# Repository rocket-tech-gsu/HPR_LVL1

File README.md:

# High Powered Rocket Level-1 (HPR Lvl-1):

### Classifying a Rockets according to their total impulse:
- Rockets that goes to moon/mars, or to an earth orbit are called orbital class rockets;
- Those going below 100-250Km are called sounding rockets;
- Below 100Km are called high powered rockets, but they are sub-classified:<br>
  - As per NAR(National Associatoin of Rocketry):

<u>__High Powered Rocketry in the USA:__</u><br>
FAA governs the US air space and have defined some guidelines:<br>
[Amateur Rocketry Guidelines](https://www.faa.gov/air_traffic/publications/atpubs/pham_html/chap31_section_1.html#:~:text=Class%202%20%2D%20a%20high%20power,pound%2Dseconds)

# Software Organization:
__Algorithms:__
- Noise Filtering:
  - Low pass filter
  - Butterworth filter
- Sensor Fusion:
  - State Estimators
  - Kalman filter

to be completed ...

# Design Overview:
to be written ...

# Avionics Overview:
to be written ...

# Future Experimental Functionalities/Payloads(not relevant to the HPR certifications):
- Custom Radio Communication module
- Reaction Wheel for stabilization of the Roll Axis
- Fin Control/Thrust Vector Control

<!-- ## Depricated Gameplan:
Step 1: Shortlist all of the sensors, actuators, microcontrollers, and other hardware components that would be the perfect fit for the given problem statement.<br>
Step 2: Come up with a schematic.<br>
Step 3: Write the program for each individual component.<br>
Step 4: Test all those individual parts of codes with the microcontroller on the breadboard or in the Proteus Software.<br>
Step 5: Integrate all those components together.<br>
Step 6: Perform tests.<br>
Step 7: Design a nice board, and route all the copper traces onto a PCB of the right size and shape.<br>
Step 8: Get the PCB manufactured, or manufacture it yourself.<br>
Step 9: Solder everything together.<br>

## Avionics Goals to be accomplished:
- Sensor Calibration,
- Test and initiate the telemetry and share the data through telemetry,
- Final Health checkup & report over telemetry("say ready for launch if everything is responding as it should"),
- Ignition Sequence: <br>
  - Check if the rocket is upright.<br>
  - Start logging the raw data from all sensors in the Flash memory chip.<br>
  - Buzzer n Light flash for Launch Alert. <br>
  - Update the IMU reference. <br>
  - Start the Camera Recording. <br>
  - Listen for the final confirmation signal over the Telemetry. <br>
  - Set the ignition charges to "HIGH" for 4 seconds.
- Determine the Altitude of the rocket in real time using: <br>
  - IMU(accelerometer + gyroscope) Data | Medium Low Pass Filter<br> 
  - Pressure Sensor Data | Aggressive Low Pass Filter<br>
  - GPS Z axis Data | Medium Low Pass Filter<br>
  - Convert all of the cleaned signals into Height<br>
  - Convert all of those heights into a single height using the Kalman Filter Algorithm for fusing multiple different sensors.
- Detect the apogee with the variation in height,
- Eject the parachute,
- Data logging(save the sensor locally on the flight computer),
- Location sensing,
- Landing detection,
- Stop the Camera Recording after 5 seconds,
- Send the location through the LoRa module,
- Write all of the data from flash chips to SD Card,
- Activate the buzzer after some delay. 

## Components Specifications:
__Rocket Motor:__
- Class I Rocket Motor

__Sensors:__
- Pressure Sensor: ~~BMP280 (deprecated)~~ [BMP390](https://www.adafruit.com/product/4816) | For altitude
- Accelerometer & Gyroscope: MPU6050 | For Navigation (inertial measurement unit)
- GPS Module: NEO-6M | For location sensing
- Magnetometer: GY-273 | For orientation sensing
- Camera Module: Raspberry Pi Camera Module 3 - 12MP 120 Degree | For capturing the video footage

__Signal Receiver & Transmitters:__
- nRF24
- LoRa Module

__Pyro Channels:__
- MOSFETs
- 900mAh LiPo Battery by Apogee (Model:09204)

__Microcontroller:__
- ATmega328P (deprecated)
- [ATmega328PB](https://www.microchip.com/en-us/product/atmega328pb)

__Memory:__
- Flash memory chip: FLASH - NOR Memory IC 256Mbit SPI - Quad I/O 133 MHz 16-SOIC | Storing the data reliably(soldered connections), quickly(133 MHz)
- SD card, for easier data recovery & redundancy. -->

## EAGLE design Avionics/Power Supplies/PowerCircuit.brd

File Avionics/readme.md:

# AVNIONICS:
This document contains
- Components List, &
- Avionics Pre-Integration Testing Protocol

for information about all three: Engine Test Avionics, Flight Avionics, and Ground Control Avionics.

# Components List:

### __<u>Engine Test Avionics Components:</u>__
- Load Cell Sensor(HX711 amplifier and 2024020278 Load Cell)

### __<u>Flight Avionics Components:</u>__
- Microcontroller(s):
    - ESP32 Wroom DevKit Board

- Memory Modules:
    - SD card(5V ready Micro-SD Breakout Board, from adafruit)
    - Flash Memory Chip : WQ25 Module

- Sensor Modules:
    - GPS Sensor(GT-U7 161212989 from Goouu Tech)
    - Accelerometer and Gyroscope Sensor Module(MPU6050 Module)
    - Pressure Sensor(BMP280)
    - Magnetometer Module(???)

- Camera Module:
    - HawkEye4k Camera Module

- Battery:
    - 2(in parallel) Li-Ion Cells.
    - 1 Li-Po Battery.
    
- Communication Module \*(*if time permits*):
    - Radio Frequency Module(E22 900T30D Version 2 from *EBYTE*)

### __<u>Ground Control Avionics Components:</u>__
- Microcontroller:
    - ESP32 Wroom DevKit Board

- Communication Module \*(*if time permits*):
    - Radio Frequency Module(E22 900T30D Version 2 from *EBYTE*)

- Ignition Circuit:
    - N Channel MOSFET
    - Li-Polymer Battery

# Avionics Pre-Integration Tests:
Most Chances of not getting a certification comes from the fact that

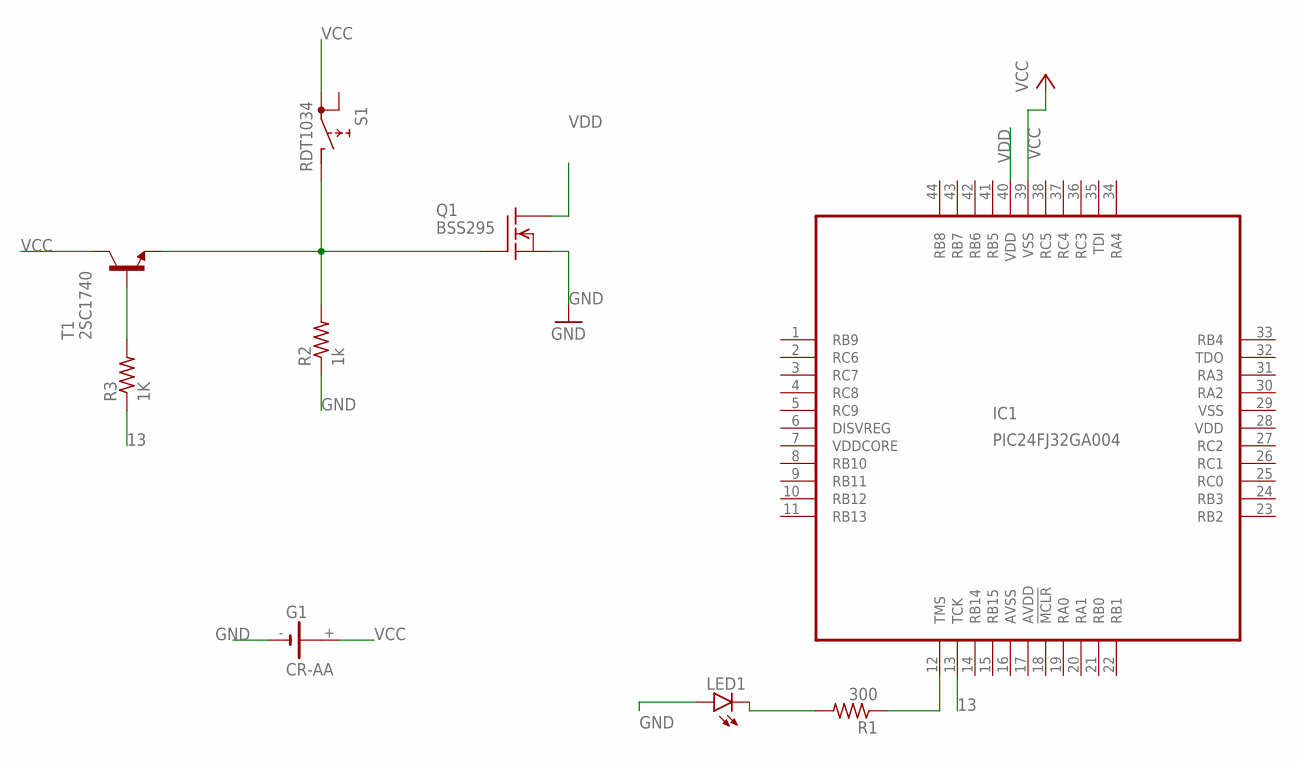
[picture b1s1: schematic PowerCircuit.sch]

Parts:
G1: CR-AA; CRAA
IC1: PIC24FJ32GA004; TQFP44
LED1: LEDCHIPLED_1206; CHIPLED_1206
Q1: BSS295; TO92
R1: 300; R01005
R2: 1k; R01005
R3: 1K; R01005
S1: RDT1034
T1: 2SC1740; TO92-ECB

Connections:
13: IC1.13 (TCK), R3.1
AVDD: IC1.17 (AVDD)
AVSS: IC1.16 (AVSS)
GND: G1.-, LED1.A, Q1.3 (S), R2.1
unnamed: R3.2, T1.B
unnamed: IC1.12 (TMS), R1.1
unnamed: Q1.1 (G), R2.2, S1.B, T1.E
unnamed: LED1.C, R1.2
VCC: G1.+, IC1.39 (VSS), S1.A1, T1.C
VDD: IC1.28 (VDD), IC1.40 (VDD), Q1.2 (D)
VDDCORE: IC1.7 (VDDCORE)
VSS: IC1.29 (VSS)

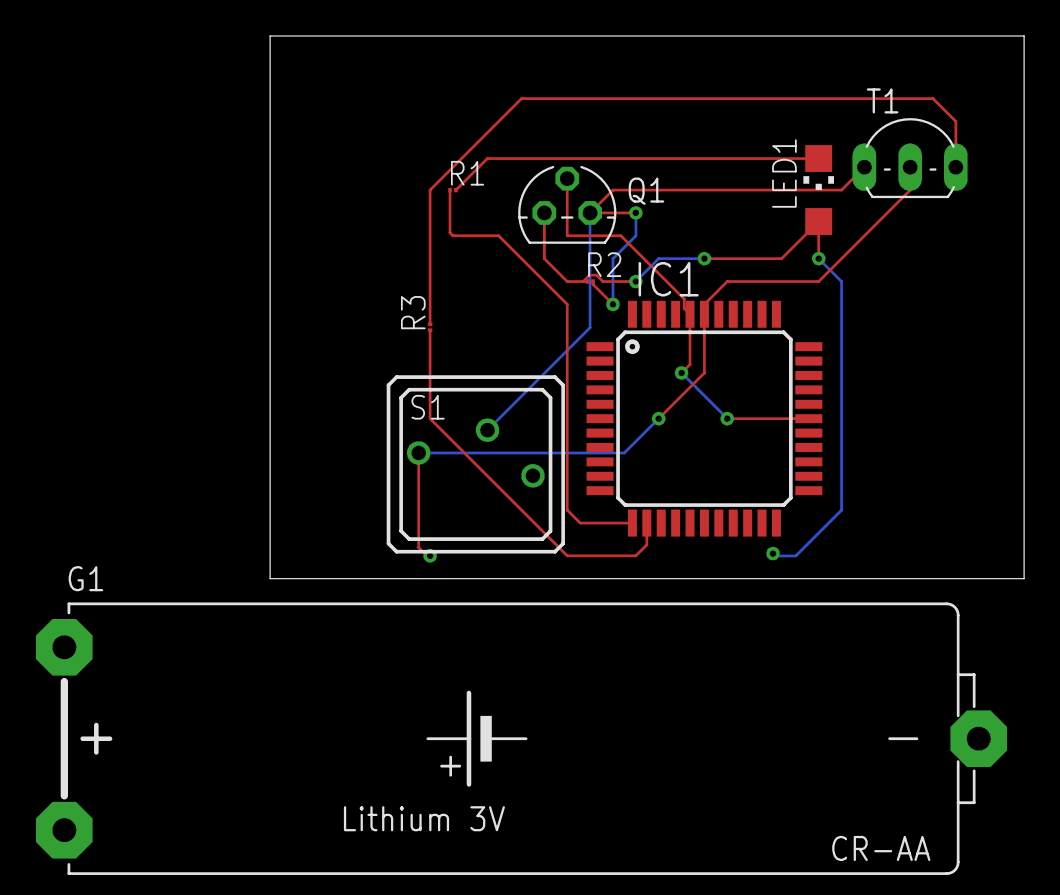
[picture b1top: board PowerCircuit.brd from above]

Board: 2 copper layers, 41.9 x 30.1 mm, 9 parts (0 on the bottom side), 8 nets.

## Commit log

2024-01-15 Readme updateREADME.md
    Component Specifications
2024-01-20 Major Update README.md
    The code architecture is changed now.
2024-01-29 Create NoseCone_HaackSeries.py
    Description - Takes in the arguments like the height of the nose cone and the Haack constant for the Hack series, then
    creates a spline as a sketch that fits the curve geometry. Then an offset curve is added to the sketch
    Which is then closed to make an area enclosing a curve. The enclosed area is then finally revolved around the axis.
2024-01-29 NoseCone_HaackSeries.py
    description update
2024-01-29 NoseCone_readme.md
2024-01-29 Move NoseCone_HaackSeries.py to MechanicalDesign/NoseCone_HaackSeries.py
2024-02-01 Refactoring
2024-02-02 Create readme.md
    This is mainly for the code breakdown of Haack_Series_NoseCone.py so that anyone can start very quickly with fusion360API without getting into the weeds of the official documentation!
2024-02-02 Update NoseCone_readme.md
    Desmos link updated from embedded link to the interactive playground link.
2024-02-06 Updated the fusion360 add-in.
2024-02-15 Fusion360_Add_In
2024-02-18 Add makefile, update MCU version
2024-02-18 Eagle Library
2024-02-18 Folder for each software, their readme files
2024-02-20 Remove litter config file
2024-02-29 eagle sachematic n board with power supply control
2024-02-29 Eagle files
2024-02-29 Create setup_readme.md
    setup documentation
2024-03-01 add CONTRIBUTERS.txt
2024-03-01 Add CONTRIBUTORS.txt
2024-03-01 Add CONTRIBUTORS.txt
    I'm the only contributor, according to this file...
    Hopefully other people add their names.
2024-03-01 Delete avionics makefile.
    This leads towards a structural change in the software organization
    for the avionics, since we'll have multiple redundant systems and need
    a separate makefile for each.
2024-03-01 Remove unnecessary whitespace.
2024-03-01 Add header to Flight Software readme
2024-03-01 Add header
2024-03-01 Mock pull request (#3)
    * Add CONTRIBUTORS.txt
    * Delete avionics makefile.
    This leads towards a structural change in the software organization
    for the avionics, since we'll have multiple redundant systems and need
    a separate makefile for each.
    * Remove unnecessary whitespace.
2024-03-02 I added my name in contributors.txt
2024-03-02 Added my name in contributors.txt
2024-03-02 Added name and email to CONTRIBUTORS.txt
2024-03-02 Update CONTRIBUTORS.txt
    added my name
2024-03-02 Added my name to CONTRIBUTORS.txt
2024-03-02 Added my name in contributors.txt (#8)
    Armaan Punjani added to CONTRIBUTORS.txt.
2024-03-02 I added my name in contributors.txt (#4)
    Add Varun Ahlawat to CONTRIBUTORS.txt.
2024-03-02 I have added my name to the contributor list
2024-03-02 I added my name
2024-03-02 name added to CONTRIBUTORS
2024-03-02 Name added to list
2024-03-02 Added name and email to CONTRIBUTORS.txt (#5)
    Add Talha Ansari to CONTRIBUTORS.txt.
2024-03-02 added name to CONTRIBUTORS.txt
2024-03-02 Update CONTRIBUTORS.txt (#6)
    Add Vijay Wulfekuhle to CONTRIBUTORS.txt
2024-03-02 my name
2024-03-02 added email address
2024-03-02 Update CONTRIBUTORS.txt
    :)
2024-03-02 added my name and email
2024-03-02 Update CONTRIBUTORS.txt (#9)
    Add Jenifer Nguyen to CONTRIBUTORS.txt.
2024-03-02 added full name
2024-03-02 Test pull request added my name (#10)
    Add Edgar to CONTRIBUTORS.txt.
2024-03-02 Added my name to CONTRIBUTORS.txt (#12)
    Add Paul Lichtenwalner to CONTRIBUTORS.txt
2024-03-02 Add CONTRIBUTORS.txt (#13)
    Add Karlissa Brown to CONTRIBUTORS.txt
2024-03-02 I have added my name to the contributor list (#16)
    Add Aryaman Boruah to CONTRIBUTORS.txt
2024-03-02 I added my name (#17)
    Add Ayo-Oluwa Sodipe to CONTRIBUTORS.txt
2024-03-02 Added name and email to CONTRIBUTORS.txt (#18)
    Add Philip Bouls to CONTRIBUTORS.txt
2024-03-02 Add Asha Hunt to CONTRIBUTORS.txt (#19)
2024-03-02 Add Brenda Samano to CONTRIBUTORS.txt (#20)
2024-03-02 Add Poorav Rawat to CONTRIBUTORS.txt (#22)
2024-03-02 Add Alexander Henriquez to CONTRIBUTORS.txt (#23)
2024-03-02 Add Nadia Thornton to CONTRIBUTORS.txt (#26)
    :)
2024-03-02 Add Tadala Kaomba to CONTRIBUTORS.txt (#27)
2024-03-02 Add Victor Googe to CONTRIBUTORS.txt (#28)
2024-03-03 Add Sabir Young to CONTRIBUTORS.txt (#21)
2024-03-03 Add Adi Pawar to CONTRIBUTORS.txt (#25)
2024-03-06 Update Readme_Designs.md
    deleted:
    >>>>>>> ada57bbd9d2ad8b40cadd9c8be98130145ac7103
2024-03-07 Update README.md
    Fix typo
2024-03-07 Add Screw Switch Library
2024-10-04 Update Repo
2024-10-17 Platform IO Software Setup
2024-10-17 Software Setup & Readme Updates
2024-10-17 readme updated
2024-11-04 Added GPS header file and serial moniter speed for GPS in Platformio.init
2024-11-06 pushing header file for bmp 280 sensor.
2024-11-06 GPS module working!!
2024-11-08 Header FIles for GY_61 accelerometer and SD_Card
2024-11-16 GPS Header FIle update
2024-11-16 Fixed a small problem with the header file for GPS
2024-11-16 SD Card header file unit tested and updated, MPU6050 header file unit tested and updated
2024-11-16 start of the flight software, written by Vijay from avionics team of the main.cpp
2024-11-19 Refactored the main.cpp and solved the platformIO linking bugs
2024-11-24 Updates GPS header file with correct pin numbers
2024-11-24 Pre-GRITS code (Chisom's contribution merge conflict resolution) (#39)
    GLHF
    * Add CONTRIBUTORS.txt
    I'm the only contributor, according to this file...
    Hopefully other people add their names.
    * Delete avionics makefile.
    This leads towards a structural change in the software organization
2024-11-24 Resolve merge conflicts
2025-02-21 Flight Software Libraries: SD-card file handling bug fixed, BMP280 library communication protocol fixed. Integrated Testing done on real hardware, STATUS: IT WORKS! Exhaustive Unit Testing for header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
2025-03-08 Milestone: Unit Testing Finished | Flight Software Written | On to logic debugging and Integrated Testing now...
2025-03-09 working data logging, and some helper/testing cpps
2025-03-21 Add HPR_LVL1 files without embedded repository
2025-03-21 Event detection implemented with Vijay: integrated testing remains
2025-04-04 Event Detection Integrated Test Successful: Latest Version
2025-04-04 MPU 9250 sensor library for AvioMk1
2025-04-06 Last flown version
2025-05-02 mg995
